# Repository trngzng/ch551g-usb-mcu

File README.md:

# About this repository
We have learned the USB MCU CH551G for educational purpose. All our documents, notes and source during the process will be stored here.

# About CH551 USB MCU
This MCU is 8-bit MCU with **built-in** USB device controller from https://www.wch.cn/. It's very cheap (**only 7.000VND - 0.31$**) but we can **directly** download the program by USB interface (*external debugger/programmer is not necessory*).

# How to use this repository
## Structure
```
+---docs
+---ref
|   \---USB_Relay_HID
\---src
    +---firmware
    \---hardware
```
1. ```docs```: contains the datasheet, notes,...
2. ```ref```: contains the reference documents and repo.
3. ```source```: 
   
   3.1. ```firmware```: contains the programs, examples, libraries,...
  
   3.2. ```hardware```: contains the schematics, PCBs of development kits and application boards.
## How to run the source
### Prerequisition
- Install [sdcc compiler](https://sourceforge.net/projects/sdcc/files/) and <a href="https://gnuwin32.sourceforge.net/packages/make.htm" target="_blank">Makefile</a>.
- Install [WCHISPTool](https://www.wch-ic.com/downloads/WCHISPTool_Setup_exe.html) for programs downloading.
### Compile the program
- Use following command for compile the program
```shell
sdcc -c main.c
sdcc main.rel
packihx main.rel > main.hex
```
- Or you can create the Makefile for automating it. All output files are in the ```output``` directory.
```make
# Define output directory
OUTPUT_DIR = output

# Compile each .c file into .rel files
hex: main.rel
	sdcc $(OUTPUT_DIR)\main.rel -o $(OUTPUT_DIR)\main.ihx

# Compile main.c to main.rel
$main.rel: main.c
	mkdir $(OUTPUT_DIR)
	sdcc -c main.c -o $(OUTPUT_DIR)\main.rel

all: hex
	packihx $(OUTPUT_DIR)\main.ihx > $(OUTPUT_DIR)\main.hex

clean:
	rmdir /s /q $(OUTPUT_DIR)
```
### Program the chip

**Note:** *To program the chip:* Keep D+ pin of MCU in high level before suppling the power of MCU. It makes CH551G entering the programming mode.
# Contributors
1. Giang Phan Truong
2. Khoa Dong Thanh
3. Tuan Pham Ho Anh

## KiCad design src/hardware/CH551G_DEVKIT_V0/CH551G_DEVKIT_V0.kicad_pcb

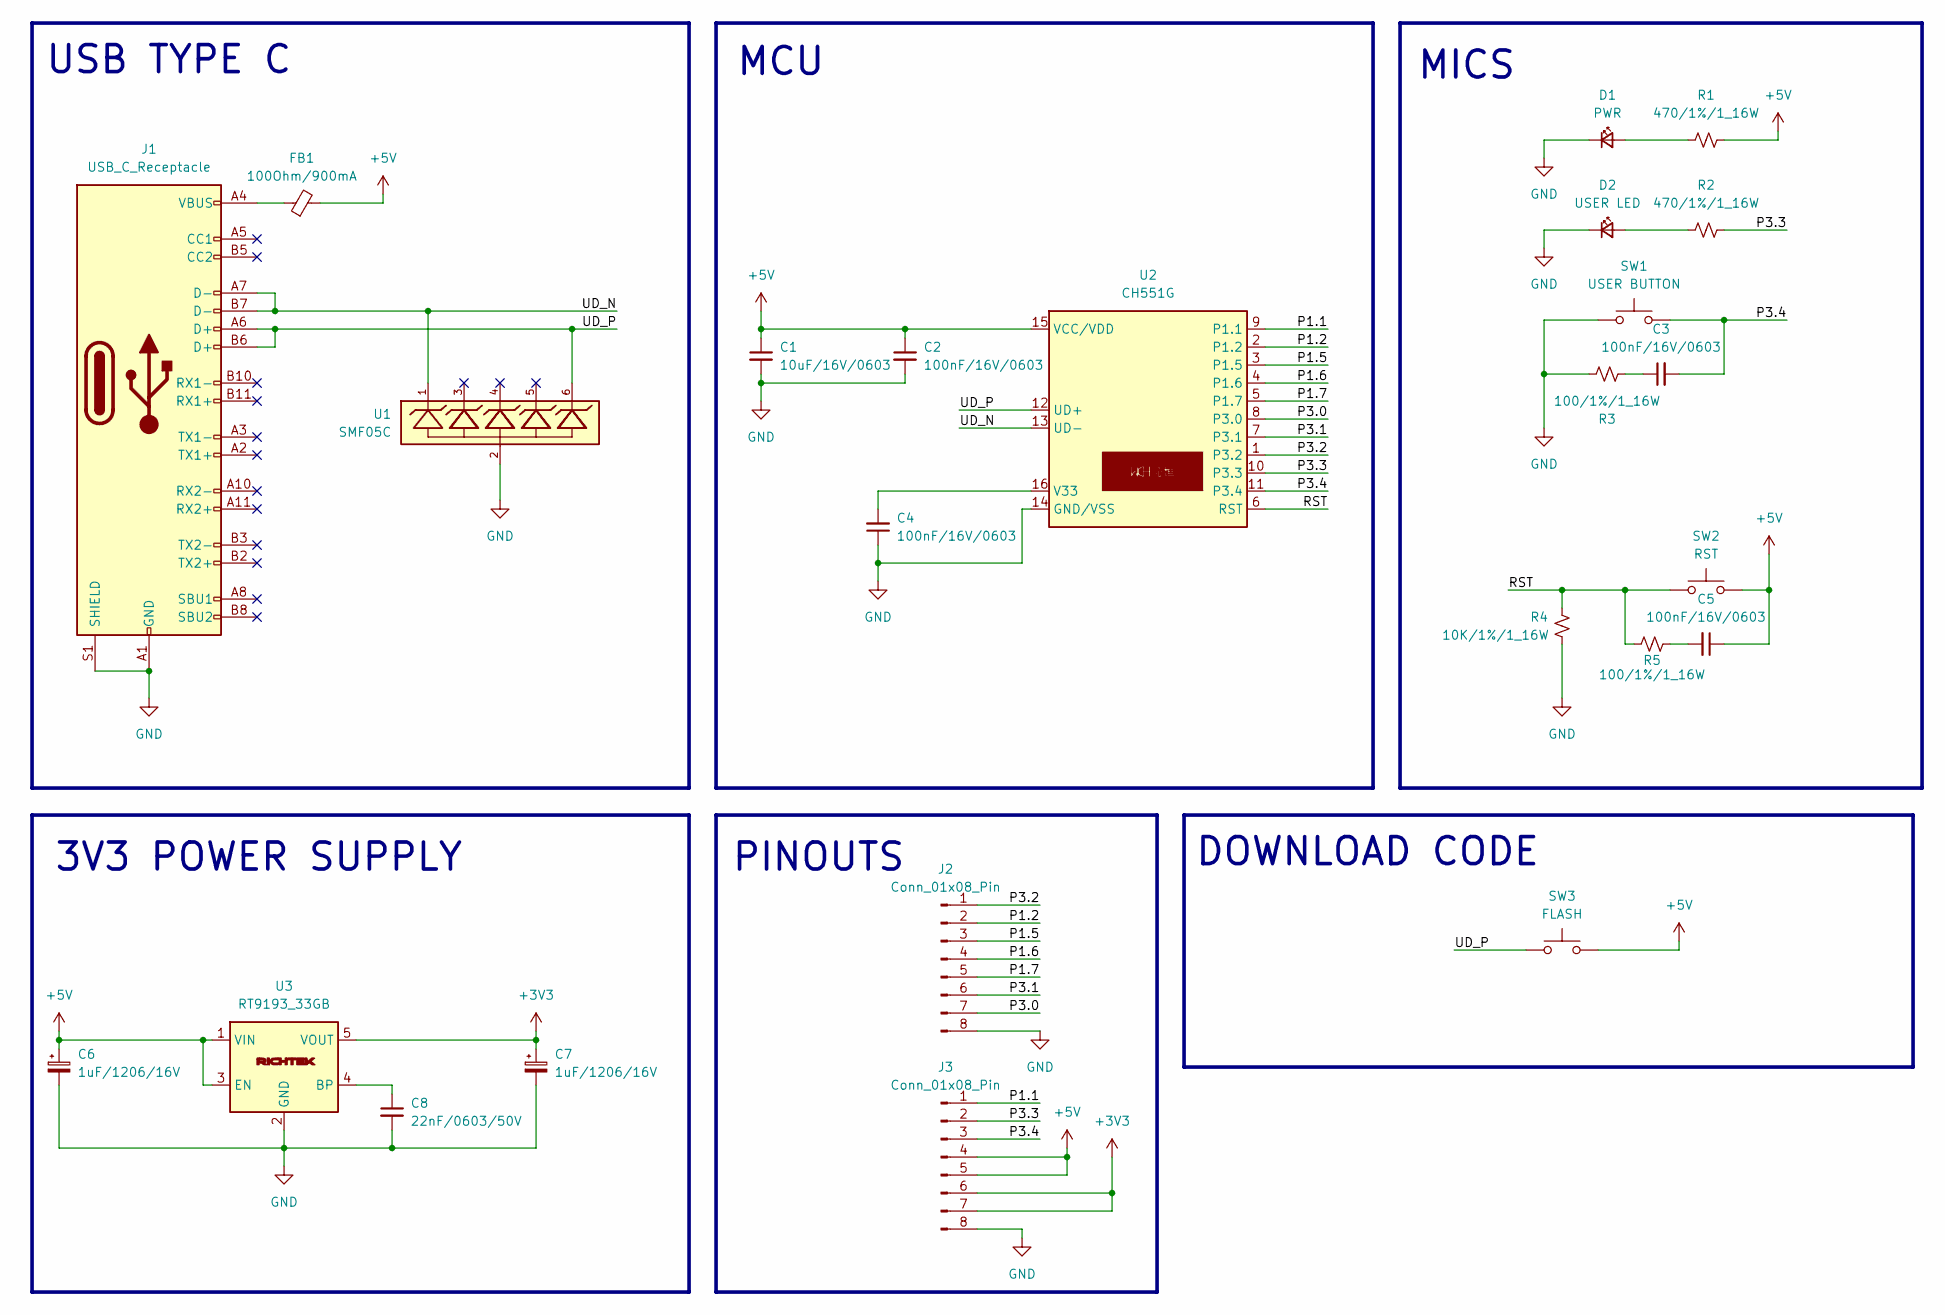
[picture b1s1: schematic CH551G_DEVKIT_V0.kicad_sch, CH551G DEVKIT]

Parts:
C1: 10uF/16V/0603; C_0603_1608Metric
C2, C3, C4, C5: 100nF/16V/0603; C_0603_1608Metric
C6, C7: 1uF/1206/16V; C_1206_3216Metric
C8: 22nF/0603/50V; C_0603_1608Metric
D1: PWR; LED_0805_2012Metric
D2: USER LED; LED_0805_2012Metric
FB1: 100Ohm/900mA; L_0805_2012Metric
J1: USB_C_Receptacle; USB_C_Receptacle_Amphenol_12401548E4-2A
J2, J3: Conn_01x08_Pin; PinHeader_1x08_P2.54mm_Vertical
R1, R2: 470/1%/1_16W; R_0402_1005Metric
R3, R5: 100/1%/1_16W; R_0402_1005Metric
R4: 10K/1%/1_16W; R_0402_1005Metric
SW1: USER BUTTON; SW_SMD
SW2: RST; SW_SMD
SW3: FLASH; SW_SMD
U1: SMF05C; SOT-363_SC-70-6
U2: CH551G; SOIC-16_3.9x9.9mm_P1.27mm
U3: RT9193_33GB; SOT-23-5

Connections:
+3V3: C7.1, J3.6, J3.7, U3.5 (VOUT)
+5V: C1.1, C2.1, C5.1, C6.1, FB1.2, J3.4, J3.5, R1.2, SW2.2, SW3.2, U2.15 (VCC/VDD), U3.1 (VIN), U3.3 (EN)
/P1.1: J3.1, U2.9 (P1.1)
/P1.2: J2.2, U2.2 (P1.2)
/P1.5: J2.3, U2.3 (P1.5)
/P1.6: J2.4, U2.4 (P1.6)
/P1.7: J2.5, U2.5 (P1.7)
/P3.0: J2.7, U2.8 (P3.0)
/P3.1: J2.6, U2.7 (P3.1)
/P3.2: J2.1, U2.1 (P3.2)
/P3.3: J3.2, R2.2, U2.10 (P3.3)
/P3.4: C3.2, J3.3, SW1.1, U2.11 (P3.4)
/RST: R4.2, R5.1, SW2.1, U2.6 (RST)
/UD_N: J1.A7 (D-), J1.B7 (D-), U1.1, U2.13 (UD-)
/UD_P: J1.A6 (D+), J1.B6 (D+), SW3.1, U1.6, U2.12 (UD+)
GND: C1.2, C2.2, C4.1, C6.2, C7.2, C8.2, D1.1 (K), D2.1 (K), J1.A1 (GND), J1.A12 (GND), J1.B1 (GND), J1.B12 (GND), J1.S1 (SHIELD), J2.8, J3.8, R3.2, R4.1, SW1.2, U1.2, U2.14 (GND/VSS), U3.2 (GND)
unnamed: C3.1, R3.1
unnamed: C5.2, R5.2
unnamed: D1.2 (A), R1.1
unnamed: D2.2 (A), R2.1
unnamed: FB1.1, J1.A4 (VBUS), J1.A9 (VBUS), J1.B4 (VBUS), J1.B9 (VBUS)
unnamed: C4.2, U2.16 (V33)
unnamed: C8.1, U3.4 (BP)

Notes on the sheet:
3V3 POWER SUPPLY
DOWNLOAD CODE
PINOUTS
MICS
USB TYPE C
MCU

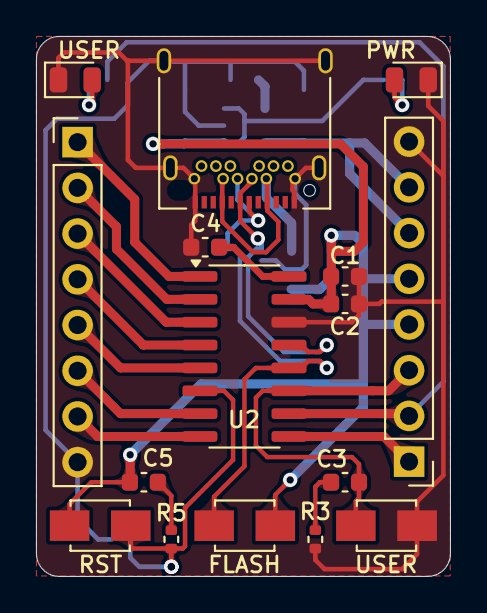
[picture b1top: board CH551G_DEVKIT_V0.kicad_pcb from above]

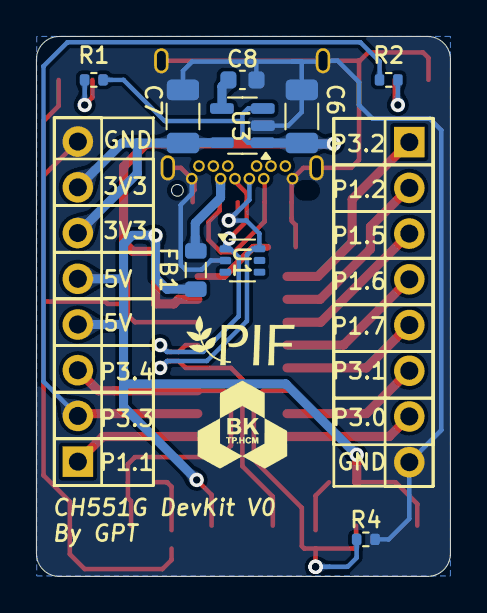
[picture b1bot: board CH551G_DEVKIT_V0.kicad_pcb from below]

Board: 2 copper layers, 23.0 x 30.0 mm, 25 parts (9 on the bottom side), 23 nets.

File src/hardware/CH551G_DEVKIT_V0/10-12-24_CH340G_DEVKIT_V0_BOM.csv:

"Reference","Value","Qty","Supply URL"
"U2","CH551G","1",""
"U3","RT9193_33GB","1","https://www.thegioiic.com/rt9193-33gb-ic-on-ap-3-3v-300ma"
"U1","SMF05C","1","https://www.thegioiic.com/smf05c-esd-protection-diode-array-sot-363"
"J1","USB_C_Receptacle","1","https://www.thegioiic.com/cong-usb-cai-3-1-type-c-24-chan-co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"
"C1","10uF/16V/0603","1","https://www.thegioiic.com/tu-gom-0603-10uf-16v"
"C2,C3,C4,C5","100nF/16V/0603","4","https://www.thegioiic.com/tu-gom-0603-100nf-0-1uf-16v"
"C6,C7","1uF/1206/16V","2","https://www.thegioiic.com/tu-tantalum-1uf-16v-1206-taja105k016rnj"
"C8","22nF/0603/50V","1","https://www.thegioiic.com/tu-gom-0603-22nf-50v"
"D1","PWR","1","https://www.thegioiic.com/led-do-1206-dan-smd-trong-suot"
"D2","USER LED","1","https://www.thegioiic.com/led-cam-0805-dan-smd-trong-suot-harvatek"
"FB1","100Ohm/900mA","1","https://www.thegioiic.com/bk2125hs101-t-ferrite-beads-100-ohm-0805"
"J2,J3","Conn_01x08_Pin","2","https://www.thegioiic.com/hang-rao-duc-don-2-54mm-40-chan-1-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"
"R1,R2","470/1%/1_16W","2","https://www.thegioiic.com/dien-tro-470-ohm-0402-1-"
"R3,R5","100/1%/1_16W","2","https://www.thegioiic.com/dien-tro-100-ohm-0402-1-"
"R4","10K/1%/1_16W","1","https://www.thegioiic.com/dien-tro-10-kohm-0402-1-"
"SW1","USER BUTTON","1","https://www.thegioiic.com/nut-nhan-3x4mm-cao-2-5mm-2-chan-smd"
"SW2","RST","1","https://www.thegioiic.com/nut-nhan-3x4mm-cao-2-5mm-2-chan-smd"
"SW3","FLASH","1","https://www.thegioiic.com/nut-nhan-3x4mm-cao-2-5mm-2-chan-smd"

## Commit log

2024-12-10 chore
2024-12-26 chore: commit the stuffs
2024-12-26 docs(README): Introduce the repo
2024-12-26 update(LIB): Add registers defination and makefile template
2024-12-26 docs(README): Update requirements for source building
2024-12-26 update(BLINK_LED): Apply the template
2024-12-26 update(MAIN): Blink LED with 1s period
2024-12-26 update(COMPILE): Create makefile for compilation sequence
2024-12-27 docs(FLASH): Update how to program the chip
2024-12-27 update(TIMER): Change timer0 config to 16-bit counter
2024-12-27 update(IGNORE): Ignore build directory
2024-12-27 update(IGNORE): Ignore references directory
